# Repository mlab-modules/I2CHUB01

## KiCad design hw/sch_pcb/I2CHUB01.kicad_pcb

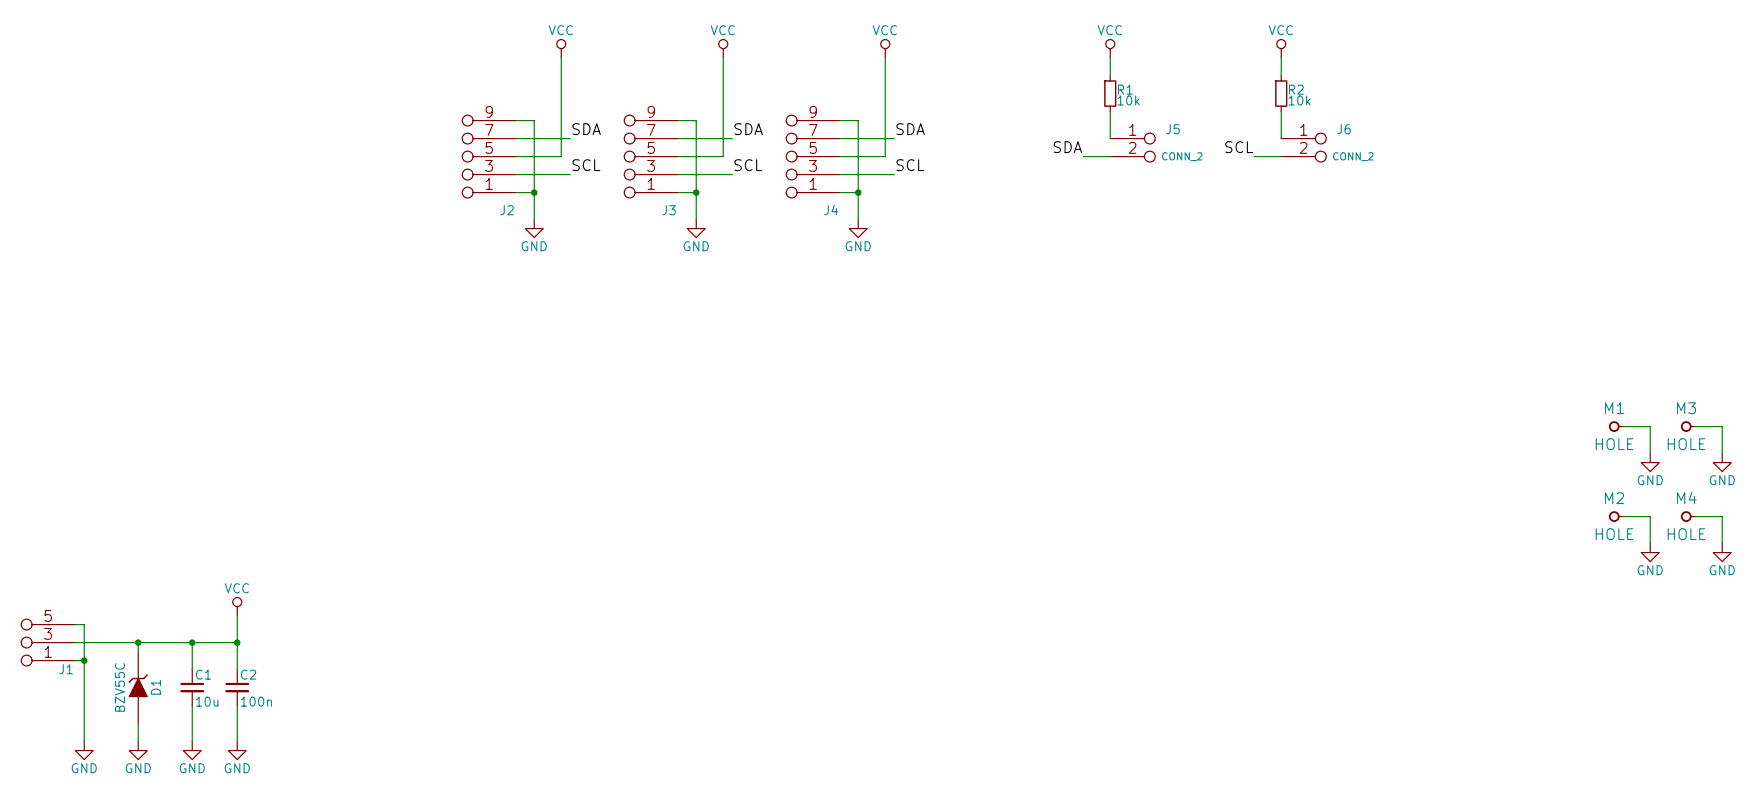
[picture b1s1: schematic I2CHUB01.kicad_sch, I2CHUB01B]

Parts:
C1: 10u; SMD-0805
C2: 100n; SMD-0805
D1: BZV55C; Diode-MiniMELF_Standard
J1: JUMP_3X2; Straight_2x03
J2, J3, J4: JUMP_5X2; Straight_2x05
J5, J6: CONN_2; Straight_1x02
M1, M2, M3, M4: HOLE; MountingHole_3mm
R1, R2: 10k; SMD-0805

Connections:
/SCL: J2.3 (4), J2.4, J3.3 (4), J3.4, J4.3 (4), J4.4, J6.2 (PM)
/SDA: J2.7, J2.8 (7), J3.7, J3.8 (7), J4.7, J4.8 (7), J5.2 (PM)
GND: C1.2, C2.2, D1.1 (A), J1.1 (2), J1.2, J1.5 (6), J1.6, J2.1 (2), J2.2, J2.9 (10), J2.10, J3.1 (2), J3.2, J3.9 (10), J3.10, J4.1 (2), J4.2, J4.9 (10), J4.10, M1.1, M2.1, M3.1, M4.1
unnamed: J5.1, R1.2
unnamed: J6.1, R2.2
VCC: C1.1, C2.1, D1.2 (K), J1.3 (4), J1.4, J2.5 (6), J2.6, J3.5 (6), J3.6, J4.5 (6), J4.6, R1.1, R2.1

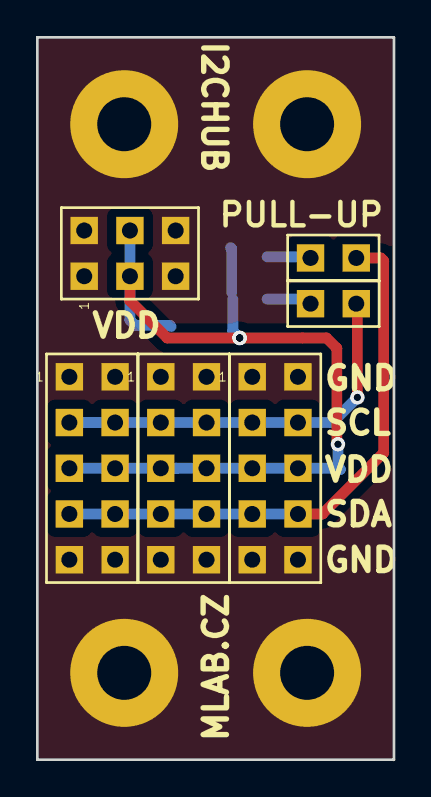
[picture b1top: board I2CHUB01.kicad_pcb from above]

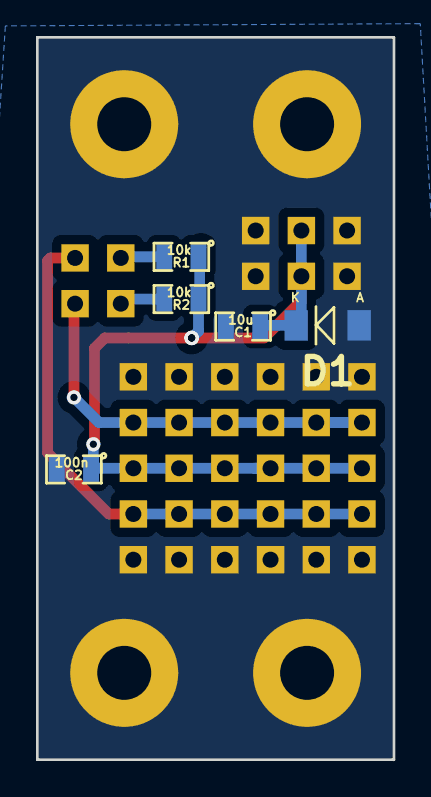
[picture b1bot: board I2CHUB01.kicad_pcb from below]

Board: 2 copper layers, 19.8 x 40.1 mm, 15 parts (5 on the bottom side), 6 nets.

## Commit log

2023-04-01 Adding force option to enable splitting in not fresh copy of Modules repository.
2023-07-04 automated commit; add github actions
2023-07-04 Update workflow files
2023-07-04 Update metadata files
2023-07-05 automated commit; rename source files to new naming convence
2023-09-16 Update status
2023-09-17 Convert project to KiCAD7.
2023-09-17 Update actions products
2023-09-17 Update metadata.yaml
    Select title image.
